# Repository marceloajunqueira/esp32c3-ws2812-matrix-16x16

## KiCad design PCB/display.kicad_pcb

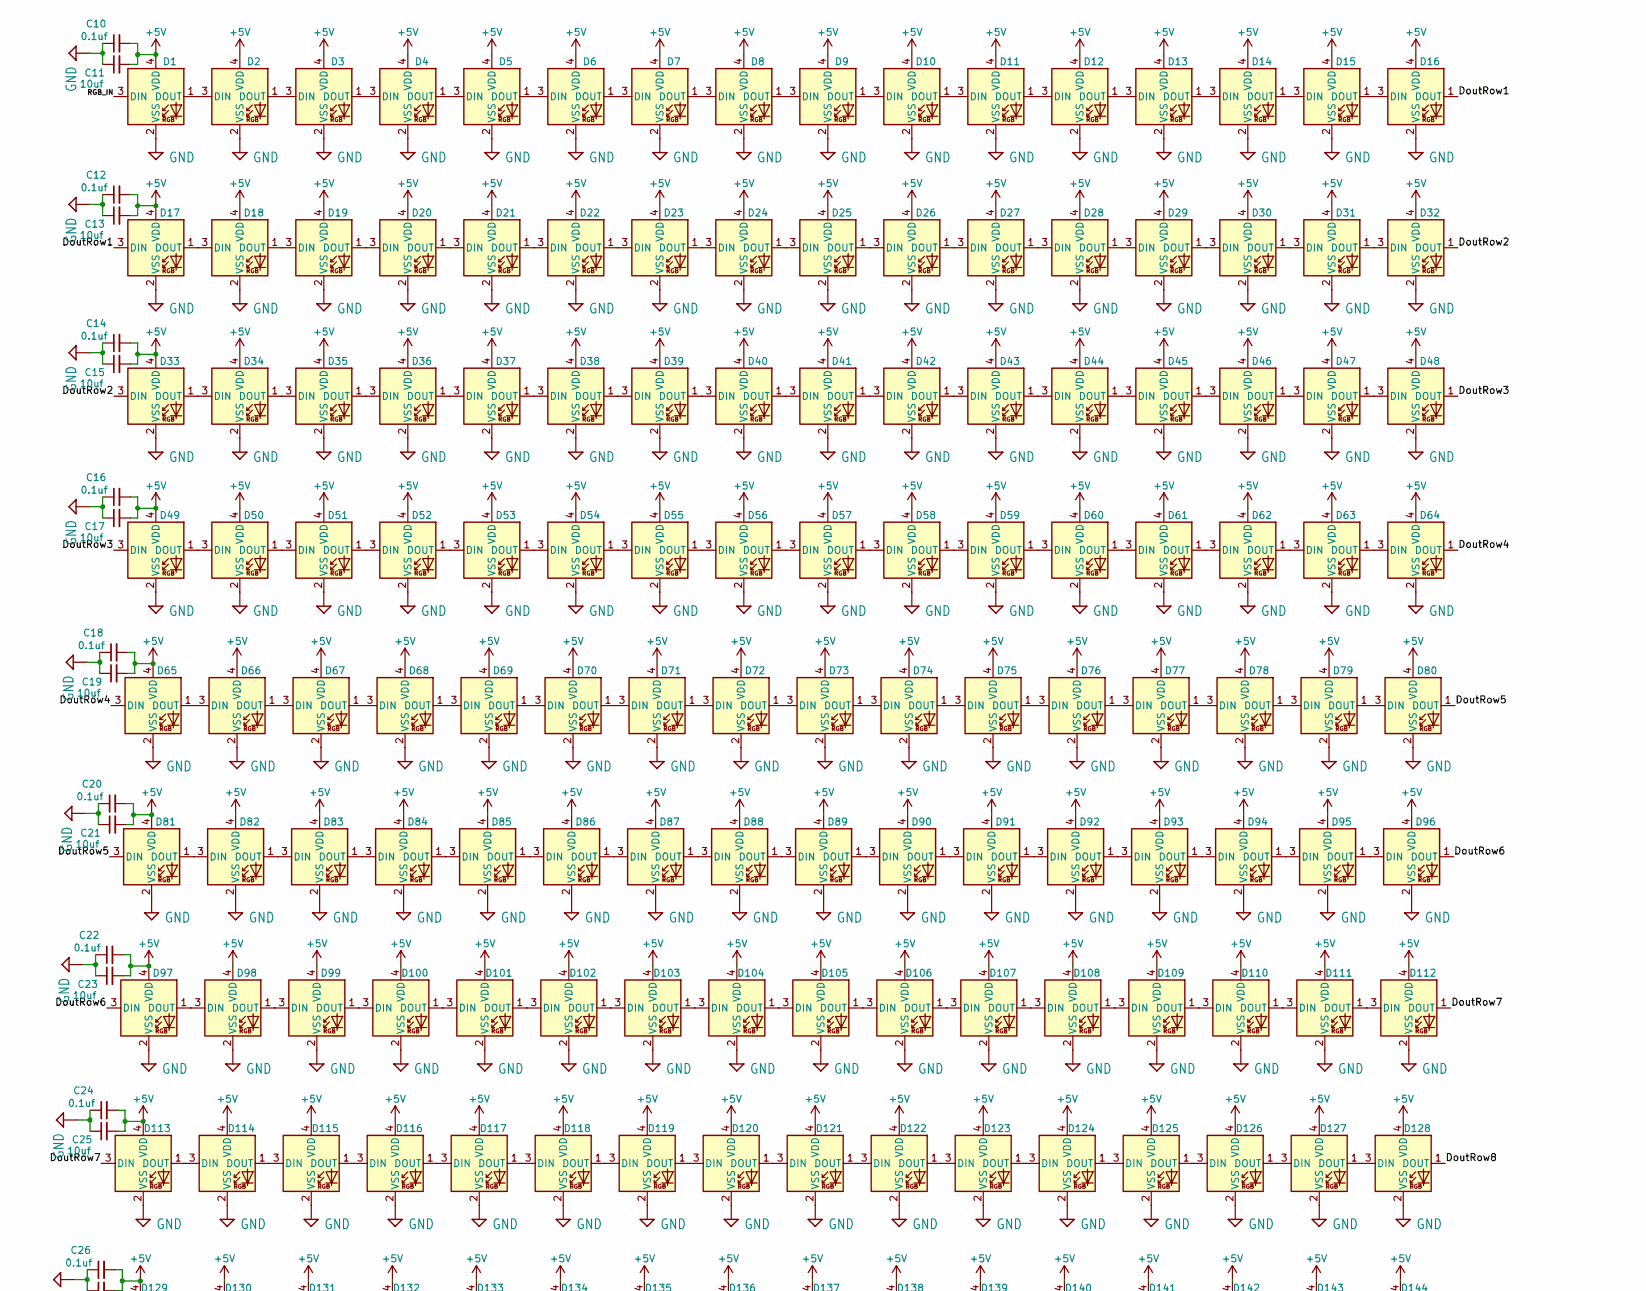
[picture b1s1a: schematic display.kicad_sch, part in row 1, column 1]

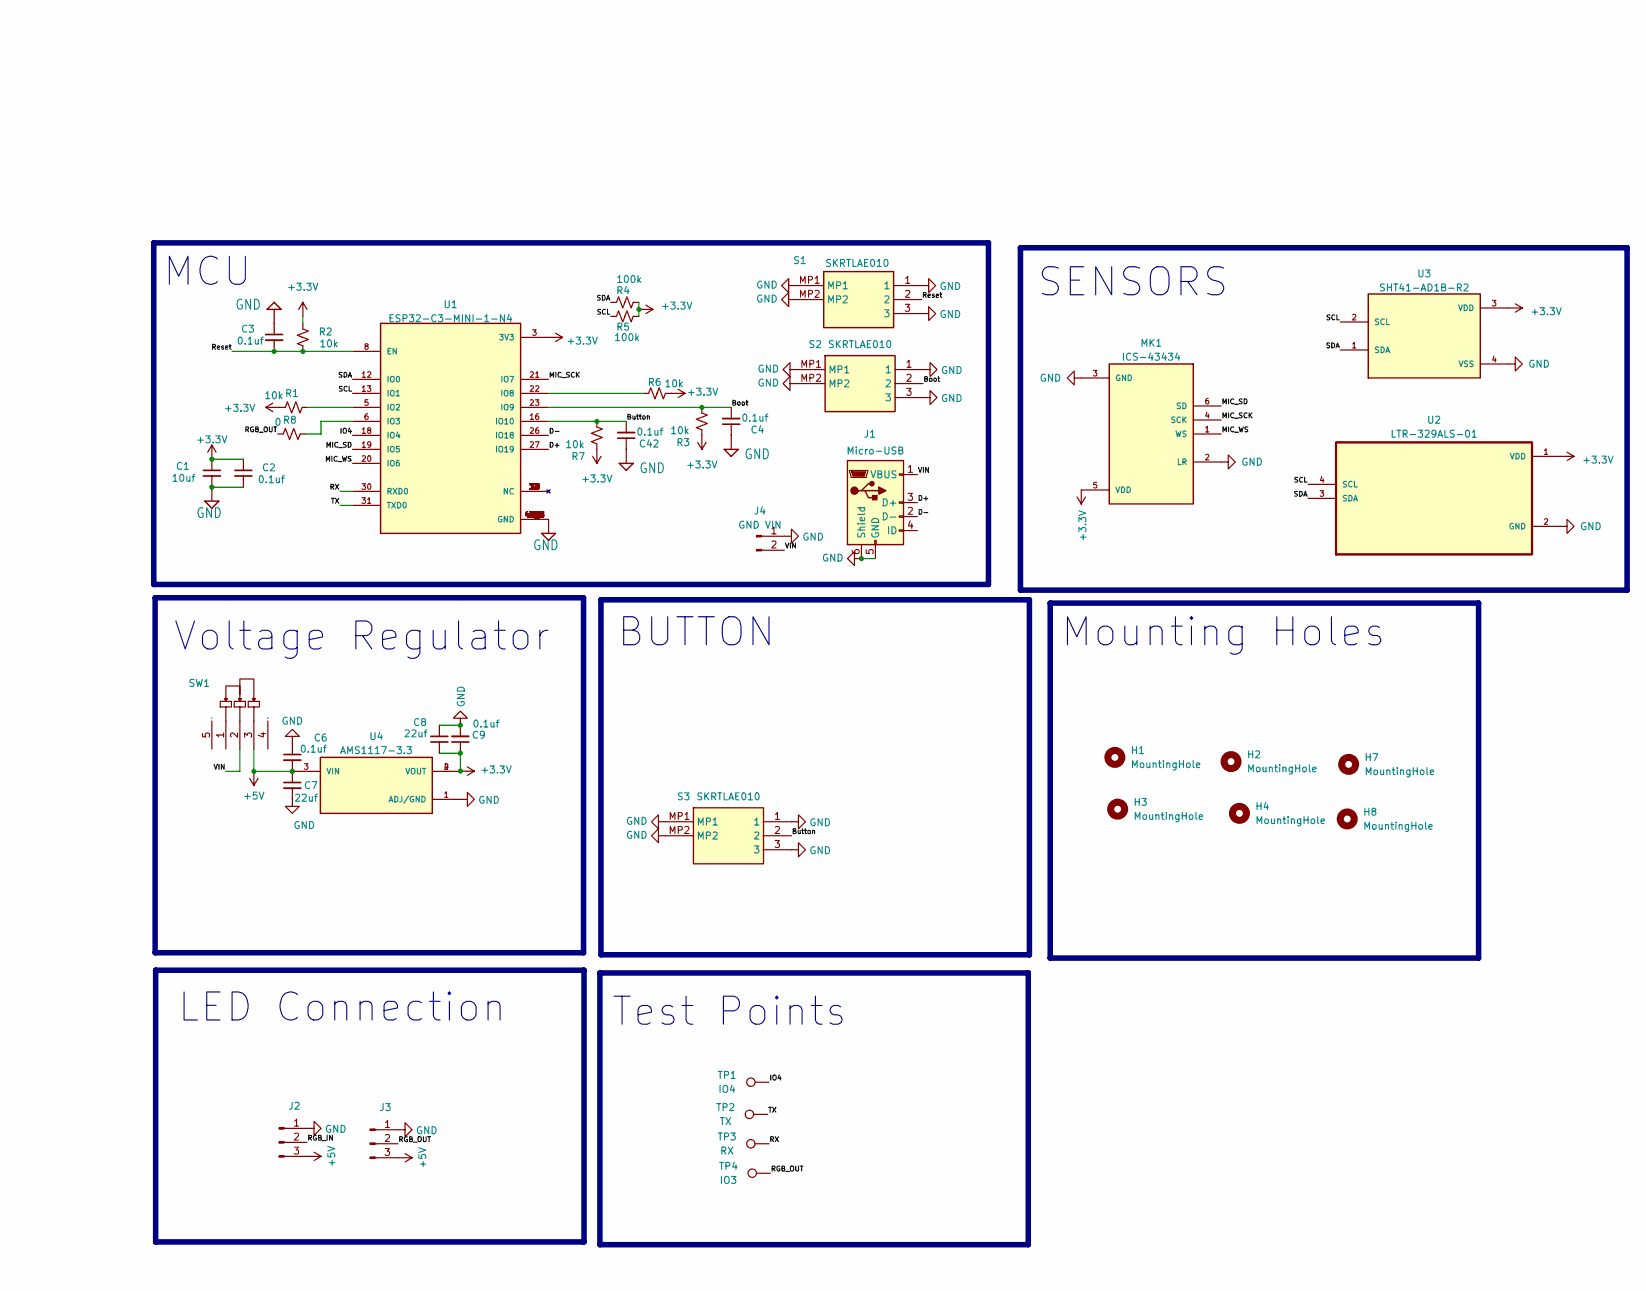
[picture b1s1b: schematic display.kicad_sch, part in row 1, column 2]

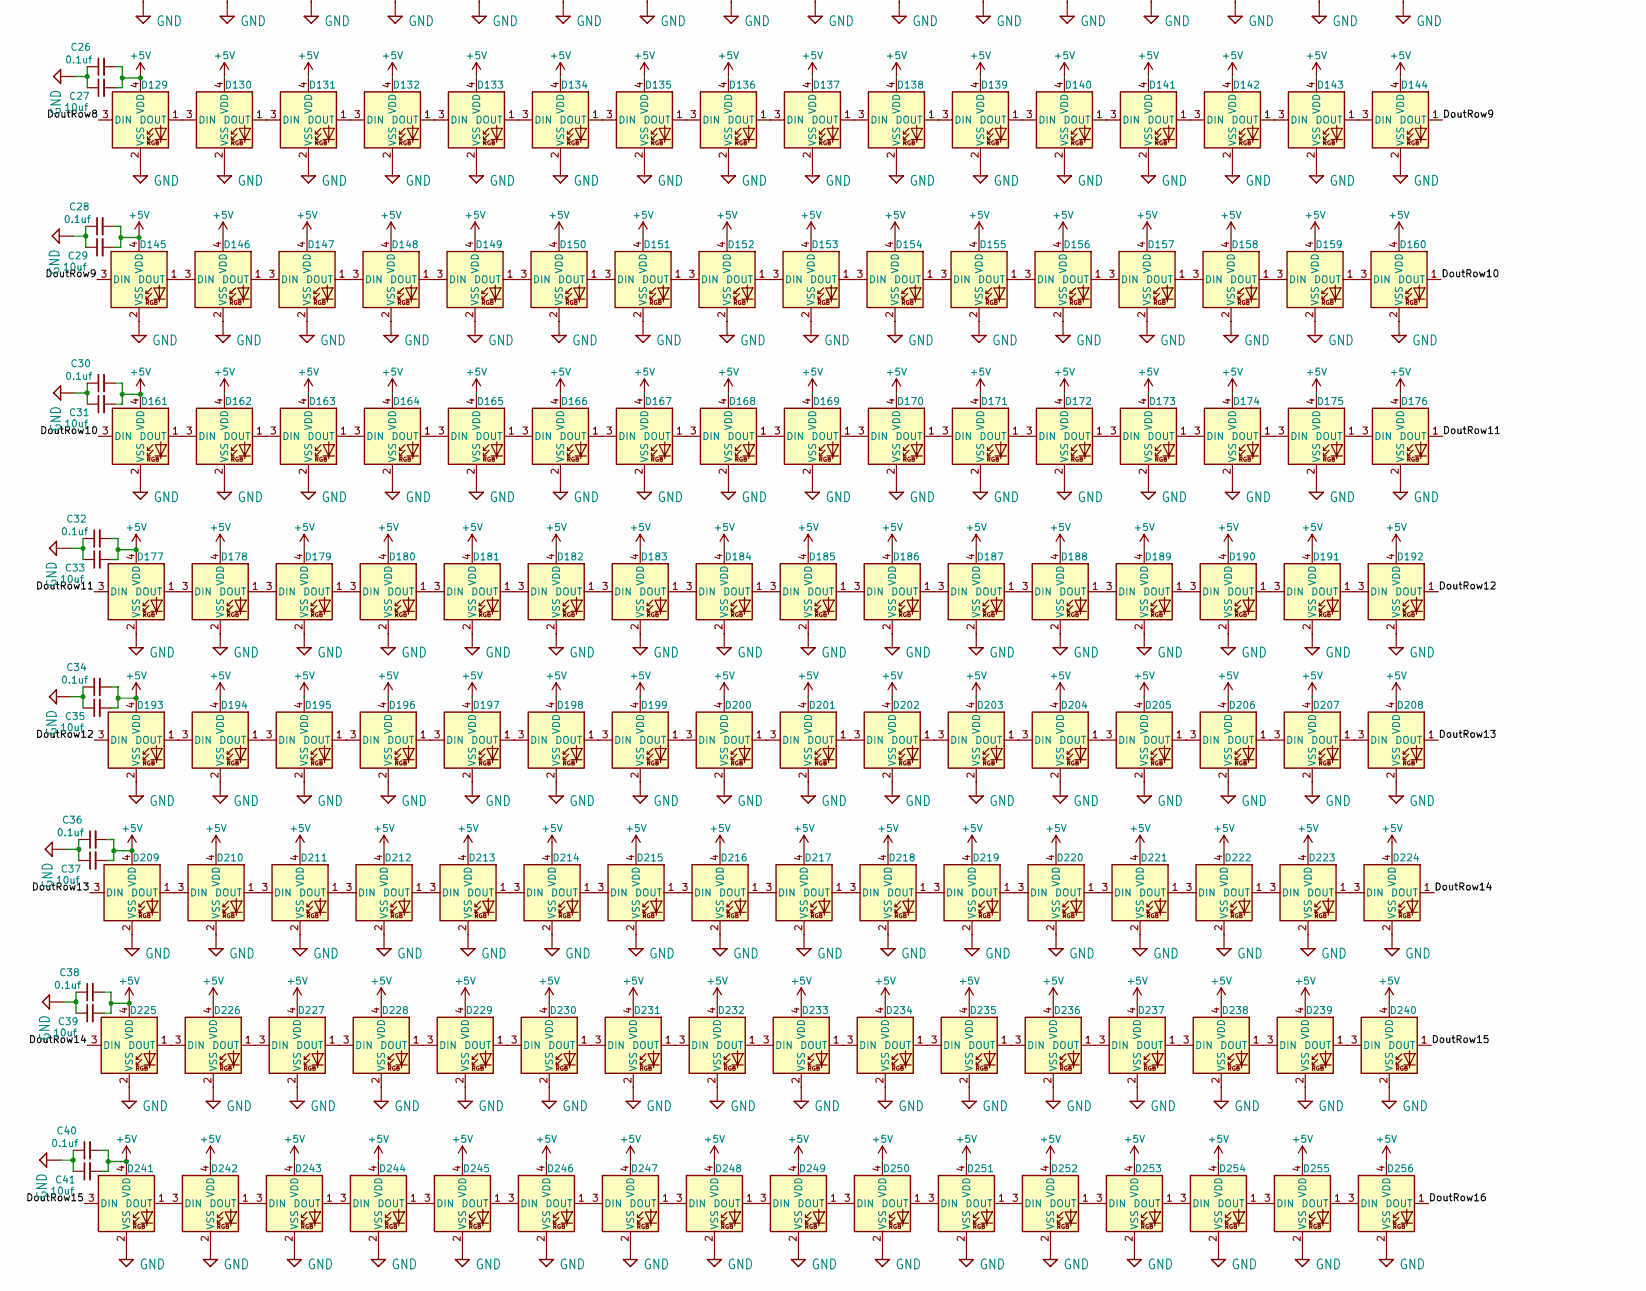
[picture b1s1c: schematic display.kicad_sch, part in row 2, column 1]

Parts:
C1: 10uf; C_0603_1608Metric; MPN CC0603MRX5R6BB106
C2, C3, C4, C6, C9, C10, C12, C14, C16, C18, C20, C22, C24, C26, C28, C30, C32, C34, C36, C38, C40, C42: 0.1uf; C_0603_1608Metric; MPN CC0603KRX7R9BB104
C7, C8: 22uf; C_1206_3216Metric; MPN T55A226M6R3C0500
C11, C13, C15, C17, C19, C21, C23, C25, C27, C29, C31, C33, C35, C37, C39, C41: 10uf; C_0603_1608Metric; MPN CC0603KRX7R9BB104
D1, D2, D3, D4, D5, D6, D7, D8, D9, D10, D11, D12, D13, D14, D15, D16, D17, D18, D19, D20, D21, D22, D23, D24, D25, D26, D27, D28, D29, D30, D31, D32, D33, D34, D35, D36, D37, D38, D39, D40, D41, D42, D43, D44, D45, D46, D47, D48, D49, D50, D51, D52, D53, D54, D55, D56, D57, D58, D59, D60, D61, D62, D63, D64, D65, D66, D67, D68, D69, D70, D71, D72, D73, D74, D75, D76, D77, D78, D79, D80, D81, D82, D83, D84, D85, D86, D87, D88, D89, D90, D91, D92, D93, D94, D95, D96, D97, D98, D99, D100, D101, D102, D103, D104, D105, D106, D107, D108, D109, D110, D111, D112, D113, D114, D115, D116, D117, D118, D119, D120, D121, D122, D123, D124, D125, D126, D127, D128, D129, D130, D131, D132, D133, D134, D135, D136, D137, D138, D139, D140, D141, D142, D143, D144, D145, D146, D147, D148, D149, D150, D151, D152, D153, D154, D155, D156, D157, D158, D159, D160, D161, D162, D163, D164, D165, D166, D167, D168, D169, D170, D171, D172, D173, D174, D175, D176, D177, D178, D179, D180, D181, D182, D183, D184, D185, D186, D187, D188, D189, D190, D191, D192, D193, D194, D195, D196, D197, D198, D199, D200, D201, D202, D203, D204, D205, D206, D207, D208, D209, D210, D211, D212, D213, D214, D215, D216, D217, D218, D219, D220, D221, D222, D223, D224, D225, D226, D227, D228, D229, D230, D231, D232, D233, D234, D235, D236, D237, D238, D239, D240, D241, D242, D243, D244, D245, D246, D247, D248, D249, D250, D251, D252, D253, D254, D255, D256: WS2812B-2020; WS2812B2020
H1, H2, H3, H4, H7, H8: MountingHole; MountingHole_2.7mm_M2.5_DIN965
J1: Micro-USB; USB_Micro-B_Molex-105017-0001; MPN 105017-0001
J2, J3: Conn_01x03_Pin; PinHeader_1x03_P2.54mm_Vertical
J4: GND VIN; PinHeader_1x02_P2.54mm_Vertical
MK1: ICS-43434; MIC_ICS-43434; MPN ICS-43434
R1, R2, R3, R6, R7: 10k; R_0603_1608Metric; MPN RC0603FR-0710KL
R4, R5: 100k; R_0603_1608Metric; MPN RC0603FR-07100KL
R8: 0; R_0603_1608Metric; MPN RC0603FR-0710KL
S1, S2, S3: SKRTLAE010; MPN SKRTLAE010
SW1: SW-TH_SK12D07VG3; MPN SK12D07VG3
TP1: IO4; TestPoint_Pad_D1.0mm
TP2: TX; TestPoint_Pad_D1.0mm
TP3: RX; TestPoint_Pad_D1.0mm
TP4: IO3; TestPoint_Pad_D1.0mm
U1: ESP32-C3-MINI-1-N4; XCVR_ESP32-C3-MINI-1-N4; MPN ESP32-C3-MINI-1-N4
U2: LTR-329ALS-01; SENSOR_LTR-329ALS-01; MPN LTR-329ALS-01
U3: SHT41-AD1B-R2; SHT4X; MPN SHT41-AD1B-R2
U4: AMS1117-3.3; SOT229P700X180-4N; MPN AMS1117-3.3

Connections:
+3.3V: C1.1, C2.1, C8.2, C9.1, MK1.5 (VDD), R1.2, R2.2, R3.2, R4.1, R5.1, R6.2, R7.2, U1.3 (3V3), U2.1 (VDD), U3.3 (VDD), U4.2 (VOUT), U4.4 (VOUT)
+5V: C6.2, C7.1, C10.2, C11.2, C12.2, C13.2, C14.2, C15.2, C16.2, C17.2, C18.2, C19.2, C20.2, C21.2, C22.2, C23.2, C24.2, C25.2, C26.2, C27.2, C28.2, C29.2, C30.2, C31.2, C32.2, C33.2, C34.2, C35.2, C36.2, C37.2, C38.2, C39.2, C40.2, C41.2, D1.4 (VDD), D2.4 (VDD), D3.4 (VDD), D4.4 (VDD), D5.4 (VDD), D6.4 (VDD), D7.4 (VDD), D8.4 (VDD), D9.4 (VDD), D10.4 (VDD), D11.4 (VDD), D12.4 (VDD), D13.4 (VDD), D14.4 (VDD), D15.4 (VDD), D16.4 (VDD), D17.4 (VDD), D18.4 (VDD), D19.4 (VDD), D20.4 (VDD), D21.4 (VDD), D22.4 (VDD), D23.4 (VDD), D24.4 (VDD), D25.4 (VDD), D26.4 (VDD), D27.4 (VDD), D28.4 (VDD), D29.4 (VDD), D30.4 (VDD), D31.4 (VDD), D32.4 (VDD), D33.4 (VDD), D34.4 (VDD), D35.4 (VDD), D36.4 (VDD), D37.4 (VDD), D38.4 (VDD), D39.4 (VDD), D40.4 (VDD), D41.4 (VDD), D42.4 (VDD), D43.4 (VDD), D44.4 (VDD), D45.4 (VDD), D46.4 (VDD), D47.4 (VDD), D48.4 (VDD), D49.4 (VDD), D50.4 (VDD), D51.4 (VDD), D52.4 (VDD), D53.4 (VDD), D54.4 (VDD), D55.4 (VDD), D56.4 (VDD), D57.4 (VDD), D58.4 (VDD), D59.4 (VDD), D60.4 (VDD), D61.4 (VDD), D62.4 (VDD), D63.4 (VDD), D64.4 (VDD), D65.4 (VDD), D66.4 (VDD), D67.4 (VDD), D68.4 (VDD), D69.4 (VDD), D70.4 (VDD), D71.4 (VDD), D72.4 (VDD), D73.4 (VDD), D74.4 (VDD), D75.4 (VDD), D76.4 (VDD), D77.4 (VDD), D78.4 (VDD), D79.4 (VDD), D80.4 (VDD), D81.4 (VDD), D82.4 (VDD), D83.4 (VDD), D84.4 (VDD), D85.4 (VDD), D86.4 (VDD), D87.4 (VDD), D88.4 (VDD), D89.4 (VDD), D90.4 (VDD), D91.4 (VDD), D92.4 (VDD), D93.4 (VDD), D94.4 (VDD), D95.4 (VDD), D96.4 (VDD), D97.4 (VDD), D98.4 (VDD), D99.4 (VDD), D100.4 (VDD), D101.4 (VDD), D102.4 (VDD), D103.4 (VDD), D104.4 (VDD), D105.4 (VDD), D106.4 (VDD), D107.4 (VDD), D108.4 (VDD), D109.4 (VDD), D110.4 (VDD), D111.4 (VDD), D112.4 (VDD), D113.4 (VDD), D114.4 (VDD), D115.4 (VDD), D116.4 (VDD), D117.4 (VDD), D118.4 (VDD), D119.4 (VDD), D120.4 (VDD), D121.4 (VDD), D122.4 (VDD), D123.4 (VDD), D124.4 (VDD), D125.4 (VDD), D126.4 (VDD), D127.4 (VDD), D128.4 (VDD), D129.4 (VDD), D130.4 (VDD), D131.4 (VDD), D132.4 (VDD), D133.4 (VDD), D134.4 (VDD), D135.4 (VDD), D136.4 (VDD), D137.4 (VDD), D138.4 (VDD), D139.4 (VDD), D140.4 (VDD), D141.4 (VDD), D142.4 (VDD), D143.4 (VDD), D144.4 (VDD), D145.4 (VDD), D146.4 (VDD), D147.4 (VDD), D148.4 (VDD), D149.4 (VDD), D150.4 (VDD), D151.4 (VDD), D152.4 (VDD), D153.4 (VDD), D154.4 (VDD), D155.4 (VDD), D156.4 (VDD), D157.4 (VDD), D158.4 (VDD), D159.4 (VDD), D160.4 (VDD), D161.4 (VDD), D162.4 (VDD), D163.4 (VDD), D164.4 (VDD), D165.4 (VDD), D166.4 (VDD), D167.4 (VDD), D168.4 (VDD), D169.4 (VDD), D170.4 (VDD), D171.4 (VDD), D172.4 (VDD), D173.4 (VDD), D174.4 (VDD), D175.4 (VDD), D176.4 (VDD), D177.4 (VDD), D178.4 (VDD), D179.4 (VDD), D180.4 (VDD), D181.4 (VDD), D182.4 (VDD), D183.4 (VDD), D184.4 (VDD), D185.4 (VDD), D186.4 (VDD), D187.4 (VDD), D188.4 (VDD), D189.4 (VDD), D190.4 (VDD), D191.4 (VDD), D192.4 (VDD), D193.4 (VDD), D194.4 (VDD), D195.4 (VDD), D196.4 (VDD), D197.4 (VDD), D198.4 (VDD), D199.4 (VDD), D200.4 (VDD), D201.4 (VDD), D202.4 (VDD), D203.4 (VDD), D204.4 (VDD), D205.4 (VDD), D206.4 (VDD), D207.4 (VDD), D208.4 (VDD), D209.4 (VDD), D210.4 (VDD), D211.4 (VDD), D212.4 (VDD), D213.4 (VDD), D214.4 (VDD), D215.4 (VDD), D216.4 (VDD), D217.4 (VDD), D218.4 (VDD), D219.4 (VDD), D220.4 (VDD), D221.4 (VDD), D222.4 (VDD), D223.4 (VDD), D224.4 (VDD), D225.4 (VDD), D226.4 (VDD), D227.4 (VDD), D228.4 (VDD), D229.4 (VDD), D230.4 (VDD), D231.4 (VDD), D232.4 (VDD), D233.4 (VDD), D234.4 (VDD), D235.4 (VDD), D236.4 (VDD), D237.4 (VDD), D238.4 (VDD), D239.4 (VDD), D240.4 (VDD), D241.4 (VDD), D242.4 (VDD), D243.4 (VDD), D244.4 (VDD), D245.4 (VDD), D246.4 (VDD), D247.4 (VDD), D248.4 (VDD), D249.4 (VDD), D250.4 (VDD), D251.4 (VDD), D252.4 (VDD), D253.4 (VDD), D254.4 (VDD), D255.4 (VDD), D256.4 (VDD), J2.3, J3.3, SW1.3, U4.3 (VIN)
/Boot: C4.2, R3.1, S2.2, U1.23 (IO9)
/Button: C42.2, R7.1, S3.2, U1.16 (IO10)
/D+: J1.3 (D+), U1.27 (IO19)
/D-: J1.2 (D-), U1.26 (IO18)
/DoutRow1: D16.1 (DOUT), D17.3 (DIN)
/DoutRow2: D32.1 (DOUT), D33.3 (DIN)
/DoutRow3: D48.1 (DOUT), D49.3 (DIN)
/DoutRow4: D64.1 (DOUT), D65.3 (DIN)
/DoutRow5: D80.1 (DOUT), D81.3 (DIN)
/DoutRow6: D96.1 (DOUT), D97.3 (DIN)
/DoutRow7: D112.1 (DOUT), D113.3 (DIN)
/DoutRow8: D128.1 (DOUT), D129.3 (DIN)
/DoutRow9: D144.1 (DOUT), D145.3 (DIN)
/DoutRow10: D160.1 (DOUT), D161.3 (DIN)
/DoutRow11: D176.1 (DOUT), D177.3 (DIN)
/DoutRow12: D192.1 (DOUT), D193.3 (DIN)
/DoutRow13: D208.1 (DOUT), D209.3 (DIN)
/DoutRow14: D224.1 (DOUT), D225.3 (DIN)
/DoutRow15: D240.1 (DOUT), D241.3 (DIN)
/DoutRow16: D256.1 (DOUT)
/IO4: TP1.1, U1.18 (IO4)
/MIC_SCK: MK1.4 (SCK), U1.21 (IO7)
/MIC_SD: MK1.6 (SD), U1.19 (IO5)
/MIC_WS: MK1.1 (WS), U1.20 (IO6)
/RGB_IN: D1.3 (DIN), J2.2
/RGB_OUT: J3.2, R8.2, TP4.1
/RX: TP3.1, U1.30 (RXD0)
/Reset: C3.2, R2.1, S1.2, U1.8 (EN)
/SCL: R5.2, U1.13 (IO1), U2.4 (SCL), U3.2 (SCL)
/SDA: R4.2, U1.12 (IO0), U2.3 (SDA), U3.1 (SDA)
/TX: TP2.1, U1.31 (TXD0)
/VIN: J1.1 (VBUS), J4.2, SW1.2
GND: C1.2, C2.2, C3.1, C4.1, C6.1, C7.2, C8.1, C9.2, C10.1, C11.1, C12.1, C13.1, C14.1, C15.1, C16.1, C17.1, C18.1, C19.1, C20.1, C21.1, C22.1, C23.1, C24.1, C25.1, C26.1, C27.1, C28.1, C29.1, C30.1, C31.1, C32.1, C33.1, C34.1, C35.1, C36.1, C37.1, C38.1, C39.1, C40.1, C41.1, C42.1, D1.2 (VSS), D2.2 (VSS), D3.2 (VSS), D4.2 (VSS), D5.2 (VSS), D6.2 (VSS), D7.2 (VSS), D8.2 (VSS), D9.2 (VSS), D10.2 (VSS), D11.2 (VSS), D12.2 (VSS), D13.2 (VSS), D14.2 (VSS), D15.2 (VSS), D16.2 (VSS), D17.2 (VSS), D18.2 (VSS), D19.2 (VSS), D20.2 (VSS), D21.2 (VSS), D22.2 (VSS), D23.2 (VSS), D24.2 (VSS), D25.2 (VSS), D26.2 (VSS), D27.2 (VSS), D28.2 (VSS), D29.2 (VSS), D30.2 (VSS), D31.2 (VSS), D32.2 (VSS), D33.2 (VSS), D34.2 (VSS), D35.2 (VSS), D36.2 (VSS), D37.2 (VSS), D38.2 (VSS), D39.2 (VSS), D40.2 (VSS), D41.2 (VSS), D42.2 (VSS), D43.2 (VSS), D44.2 (VSS), D45.2 (VSS), D46.2 (VSS), D47.2 (VSS), D48.2 (VSS), D49.2 (VSS), D50.2 (VSS), D51.2 (VSS), D52.2 (VSS), D53.2 (VSS), D54.2 (VSS), D55.2 (VSS), D56.2 (VSS), D57.2 (VSS), D58.2 (VSS), D59.2 (VSS), D60.2 (VSS), D61.2 (VSS), D62.2 (VSS), D63.2 (VSS), D64.2 (VSS), D65.2 (VSS), D66.2 (VSS), D67.2 (VSS), D68.2 (VSS), D69.2 (VSS), D70.2 (VSS), D71.2 (VSS), D72.2 (VSS), D73.2 (VSS), D74.2 (VSS), D75.2 (VSS), D76.2 (VSS), D77.2 (VSS), D78.2 (VSS), D79.2 (VSS), D80.2 (VSS), D81.2 (VSS), D82.2 (VSS), D83.2 (VSS), D84.2 (VSS), D85.2 (VSS), D86.2 (VSS), D87.2 (VSS), D88.2 (VSS), D89.2 (VSS), D90.2 (VSS), D91.2 (VSS), D92.2 (VSS), D93.2 (VSS), D94.2 (VSS), D95.2 (VSS), D96.2 (VSS), D97.2 (VSS), D98.2 (VSS), D99.2 (VSS), D100.2 (VSS), D101.2 (VSS), D102.2 (VSS), D103.2 (VSS), D104.2 (VSS), D105.2 (VSS), D106.2 (VSS), D107.2 (VSS), D108.2 (VSS), D109.2 (VSS), D110.2 (VSS), D111.2 (VSS), D112.2 (VSS), D113.2 (VSS), D114.2 (VSS), D115.2 (VSS), D116.2 (VSS), D117.2 (VSS), D118.2 (VSS), D119.2 (VSS), D120.2 (VSS), D121.2 (VSS), D122.2 (VSS), D123.2 (VSS), D124.2 (VSS), D125.2 (VSS), D126.2 (VSS), D127.2 (VSS), D128.2 (VSS), D129.2 (VSS), D130.2 (VSS), D131.2 (VSS), D132.2 (VSS), D133.2 (VSS), D134.2 (VSS), D135.2 (VSS), D136.2 (VSS), D137.2 (VSS), D138.2 (VSS), D139.2 (VSS), D140.2 (VSS), D141.2 (VSS), D142.2 (VSS), D143.2 (VSS), D144.2 (VSS), D145.2 (VSS), D146.2 (VSS), D147.2 (VSS), D148.2 (VSS), D149.2 (VSS), D150.2 (VSS), D151.2 (VSS), D152.2 (VSS), D153.2 (VSS), D154.2 (VSS), D155.2 (VSS), D156.2 (VSS), D157.2 (VSS), D158.2 (VSS), D159.2 (VSS), D160.2 (VSS), D161.2 (VSS), D162.2 (VSS), D163.2 (VSS), D164.2 (VSS), D165.2 (VSS), D166.2 (VSS), D167.2 (VSS), D168.2 (VSS), D169.2 (VSS), D170.2 (VSS), D171.2 (VSS), D172.2 (VSS), D173.2 (VSS), D174.2 (VSS), D175.2 (VSS), D176.2 (VSS), D177.2 (VSS), D178.2 (VSS), D179.2 (VSS), D180.2 (VSS), D181.2 (VSS), D182.2 (VSS), D183.2 (VSS), D184.2 (VSS), D185.2 (VSS), D186.2 (VSS), D187.2 (VSS), D188.2 (VSS), D189.2 (VSS), D190.2 (VSS), D191.2 (VSS), D192.2 (VSS), D193.2 (VSS), D194.2 (VSS), D195.2 (VSS), D196.2 (VSS), D197.2 (VSS), D198.2 (VSS), D199.2 (VSS), D200.2 (VSS), D201.2 (VSS), D202.2 (VSS), D203.2 (VSS), D204.2 (VSS), D205.2 (VSS), D206.2 (VSS), D207.2 (VSS), D208.2 (VSS), D209.2 (VSS), D210.2 (VSS), D211.2 (VSS), D212.2 (VSS), D213.2 (VSS), D214.2 (VSS), D215.2 (VSS), D216.2 (VSS), D217.2 (VSS), D218.2 (VSS), D219.2 (VSS), D220.2 (VSS), D221.2 (VSS), D222.2 (VSS), D223.2 (VSS), D224.2 (VSS), D225.2 (VSS), D226.2 (VSS), D227.2 (VSS), D228.2 (VSS), D229.2 (VSS), D230.2 (VSS), D231.2 (VSS), D232.2 (VSS), D233.2 (VSS), D234.2 (VSS), D235.2 (VSS), D236.2 (VSS), D237.2 (VSS), D238.2 (VSS), D239.2 (VSS), D240.2 (VSS), D241.2 (VSS), D242.2 (VSS), D243.2 (VSS), D244.2 (VSS), D245.2 (VSS), D246.2 (VSS), D247.2 (VSS), D248.2 (VSS), D249.2 (VSS), D250.2 (VSS), D251.2 (VSS), D252.2 (VSS), D253.2 (VSS), D254.2 (VSS), D255.2 (VSS), D256.2 (VSS), J1.5 (GND), J1.6 (Shield), J2.1, J3.1, J4.1, MK1.2 (LR), MK1.3 (GND), S1.1, S1.3, S1.MP1, S1.MP2, S2.1, S2.3, S2.MP1, S2.MP2, S3.1, S3.3, S3.MP1, S3.MP2, U1.1 (GND), U1.2 (GND), U1.11 (GND), U1.14 (GND), U1.36 (GND), U1.37 (GND), U1.38 (GND), U1.39 (GND), U1.40 (GND), U1.41 (GND), U1.42 (GND), U1.43 (GND), U1.44 (GND), U1.45 (GND), U1.46 (GND), U1.47 (GND), U1.48 (GND), U1.49_1 (GND), U1.49_2 (GND), U1.49_3 (GND), U1.49_4 (GND), U1.49_5 (GND), U1.49_6 (GND), U1.49_7 (GND), U1.49_8 (GND), U1.49_9 (GND), U1.50 (GND), U1.51 (GND), U1.52 (GND), U1.53 (GND), U2.2 (GND), U3.4 (VSS), U4.1 (ADJ/GND)
unnamed: D1.1 (DOUT), D2.3 (DIN)
unnamed: D2.1 (DOUT), D3.3 (DIN)
unnamed: D3.1 (DOUT), D4.3 (DIN)
unnamed: D4.1 (DOUT), D5.3 (DIN)
unnamed: D5.1 (DOUT), D6.3 (DIN)
unnamed: D6.1 (DOUT), D7.3 (DIN)
unnamed: D7.1 (DOUT), D8.3 (DIN)
unnamed: D8.1 (DOUT), D9.3 (DIN)
unnamed: D9.1 (DOUT), D10.3 (DIN)
unnamed: D10.1 (DOUT), D11.3 (DIN)
unnamed: D11.1 (DOUT), D12.3 (DIN)
unnamed: D12.1 (DOUT), D13.3 (DIN)
unnamed: D13.1 (DOUT), D14.3 (DIN)
unnamed: D14.1 (DOUT), D15.3 (DIN)
unnamed: D15.1 (DOUT), D16.3 (DIN)
unnamed: D17.1 (DOUT), D18.3 (DIN)
unnamed: D18.1 (DOUT), D19.3 (DIN)
unnamed: D19.1 (DOUT), D20.3 (DIN)
unnamed: D20.1 (DOUT), D21.3 (DIN)
unnamed: D21.1 (DOUT), D22.3 (DIN)
unnamed: D22.1 (DOUT), D23.3 (DIN)
unnamed: D23.1 (DOUT), D24.3 (DIN)
unnamed: D24.1 (DOUT), D25.3 (DIN)
unnamed: D25.1 (DOUT), D26.3 (DIN)
unnamed: D26.1 (DOUT), D27.3 (DIN)
unnamed: D27.1 (DOUT), D28.3 (DIN)
unnamed: D28.1 (DOUT), D29.3 (DIN)
unnamed: D29.1 (DOUT), D30.3 (DIN)
unnamed: D30.1 (DOUT), D31.3 (DIN)
unnamed: D31.1 (DOUT), D32.3 (DIN)
unnamed: D33.1 (DOUT), D34.3 (DIN)
unnamed: D34.1 (DOUT), D35.3 (DIN)
unnamed: D35.1 (DOUT), D36.3 (DIN)
unnamed: D36.1 (DOUT), D37.3 (DIN)
unnamed: D37.1 (DOUT), D38.3 (DIN)
unnamed: D38.1 (DOUT), D39.3 (DIN)
unnamed: D39.1 (DOUT), D40.3 (DIN)
unnamed: D40.1 (DOUT), D41.3 (DIN)
unnamed: D41.1 (DOUT), D42.3 (DIN)
unnamed: D42.1 (DOUT), D43.3 (DIN)
unnamed: D43.1 (DOUT), D44.3 (DIN)
unnamed: D44.1 (DOUT), D45.3 (DIN)
unnamed: D45.1 (DOUT), D46.3 (DIN)
unnamed: D46.1 (DOUT), D47.3 (DIN)
unnamed: D47.1 (DOUT), D48.3 (DIN)
unnamed: D49.1 (DOUT), D50.3 (DIN)
unnamed: D50.1 (DOUT), D51.3 (DIN)
unnamed: D51.1 (DOUT), D52.3 (DIN)
unnamed: D52.1 (DOUT), D53.3 (DIN)
unnamed: D53.1 (DOUT), D54.3 (DIN)
unnamed: D54.1 (DOUT), D55.3 (DIN)
unnamed: D55.1 (DOUT), D56.3 (DIN)
unnamed: D56.1 (DOUT), D57.3 (DIN)
unnamed: D57.1 (DOUT), D58.3 (DIN)
unnamed: D58.1 (DOUT), D59.3 (DIN)
unnamed: D59.1 (DOUT), D60.3 (DIN)
unnamed: D60.1 (DOUT), D61.3 (DIN)
unnamed: D61.1 (DOUT), D62.3 (DIN)
unnamed: D62.1 (DOUT), D63.3 (DIN)
unnamed: D63.1 (DOUT), D64.3 (DIN)
unnamed: D65.1 (DOUT), D66.3 (DIN)
unnamed: D66.1 (DOUT), D67.3 (DIN)
unnamed: D67.1 (DOUT), D68.3 (DIN)
unnamed: D68.1 (DOUT), D69.3 (DIN)
unnamed: D69.1 (DOUT), D70.3 (DIN)
unnamed: D70.1 (DOUT), D71.3 (DIN)
unnamed: D71.1 (DOUT), D72.3 (DIN)
unnamed: D72.1 (DOUT), D73.3 (DIN)
unnamed: D73.1 (DOUT), D74.3 (DIN)
unnamed: D74.1 (DOUT), D75.3 (DIN)
unnamed: D75.1 (DOUT), D76.3 (DIN)
unnamed: D76.1 (DOUT), D77.3 (DIN)
unnamed: D77.1 (DOUT), D78.3 (DIN)
unnamed: D78.1 (DOUT), D79.3 (DIN)
unnamed: D79.1 (DOUT), D80.3 (DIN)
unnamed: D81.1 (DOUT), D82.3 (DIN)
unnamed: D82.1 (DOUT), D83.3 (DIN)
unnamed: D83.1 (DOUT), D84.3 (DIN)
unnamed: D84.1 (DOUT), D85.3 (DIN)
unnamed: D85.1 (DOUT), D86.3 (DIN)
unnamed: D86.1 (DOUT), D87.3 (DIN)
unnamed: D87.1 (DOUT), D88.3 (DIN)
unnamed: D88.1 (DOUT), D89.3 (DIN)
unnamed: D89.1 (DOUT), D90.3 (DIN)
unnamed: D90.1 (DOUT), D91.3 (DIN)
unnamed: D91.1 (DOUT), D92.3 (DIN)
unnamed: D92.1 (DOUT), D93.3 (DIN)
unnamed: D93.1 (DOUT), D94.3 (DIN)
unnamed: D94.1 (DOUT), D95.3 (DIN)
unnamed: D95.1 (DOUT), D96.3 (DIN)
unnamed: D97.1 (DOUT), D98.3 (DIN)
unnamed: D98.1 (DOUT), D99.3 (DIN)
unnamed: D99.1 (DOUT), D100.3 (DIN)
unnamed: D100.1 (DOUT), D101.3 (DIN)
unnamed: D101.1 (DOUT), D102.3 (DIN)
unnamed: D102.1 (DOUT), D103.3 (DIN)
unnamed: D103.1 (DOUT), D104.3 (DIN)
unnamed: D104.1 (DOUT), D105.3 (DIN)
unnamed: D105.1 (DOUT), D106.3 (DIN)
unnamed: D106.1 (DOUT), D107.3 (DIN)
unnamed: D107.1 (DOUT), D108.3 (DIN)
unnamed: D108.1 (DOUT), D109.3 (DIN)
unnamed: D109.1 (DOUT), D110.3 (DIN)
unnamed: D110.1 (DOUT), D111.3 (DIN)
unnamed: D111.1 (DOUT), D112.3 (DIN)
unnamed: D113.1 (DOUT), D114.3 (DIN)
unnamed: D114.1 (DOUT), D115.3 (DIN)
unnamed: D115.1 (DOUT), D116.3 (DIN)
unnamed: D116.1 (DOUT), D117.3 (DIN)
unnamed: D117.1 (DOUT), D118.3 (DIN)
unnamed: D118.1 (DOUT), D119.3 (DIN)
unnamed: D119.1 (DOUT), D120.3 (DIN)
unnamed: D120.1 (DOUT), D121.3 (DIN)
unnamed: D121.1 (DOUT), D122.3 (DIN)
unnamed: D122.1 (DOUT), D123.3 (DIN)
unnamed: D123.1 (DOUT), D124.3 (DIN)
unnamed: D124.1 (DOUT), D125.3 (DIN)
unnamed: D125.1 (DOUT), D126.3 (DIN)
unnamed: D126.1 (DOUT), D127.3 (DIN)
unnamed: D127.1 (DOUT), D128.3 (DIN)
unnamed: D129.1 (DOUT), D130.3 (DIN)
unnamed: D130.1 (DOUT), D131.3 (DIN)
unnamed: D131.1 (DOUT), D132.3 (DIN)
unnamed: D132.1 (DOUT), D133.3 (DIN)
unnamed: D133.1 (DOUT), D134.3 (DIN)
unnamed: D134.1 (DOUT), D135.3 (DIN)
unnamed: D135.1 (DOUT), D136.3 (DIN)
unnamed: D136.1 (DOUT), D137.3 (DIN)
unnamed: D137.1 (DOUT), D138.3 (DIN)
unnamed: D138.1 (DOUT), D139.3 (DIN)
unnamed: D139.1 (DOUT), D140.3 (DIN)
unnamed: D140.1 (DOUT), D141.3 (DIN)
unnamed: D141.1 (DOUT), D142.3 (DIN)
unnamed: D142.1 (DOUT), D143.3 (DIN)
unnamed: D143.1 (DOUT), D144.3 (DIN)
unnamed: D145.1 (DOUT), D146.3 (DIN)
unnamed: D146.1 (DOUT), D147.3 (DIN)
unnamed: D147.1 (DOUT), D148.3 (DIN)
unnamed: D148.1 (DOUT), D149.3 (DIN)
unnamed: D149.1 (DOUT), D150.3 (DIN)
unnamed: D150.1 (DOUT), D151.3 (DIN)
unnamed: D151.1 (DOUT), D152.3 (DIN)
unnamed: D152.1 (DOUT), D153.3 (DIN)
unnamed: D153.1 (DOUT), D154.3 (DIN)
unnamed: D154.1 (DOUT), D155.3 (DIN)
unnamed: D155.1 (DOUT), D156.3 (DIN)
unnamed: D156.1 (DOUT), D157.3 (DIN)
unnamed: D157.1 (DOUT), D158.3 (DIN)
unnamed: D158.1 (DOUT), D159.3 (DIN)
unnamed: D159.1 (DOUT), D160.3 (DIN)
unnamed: D161.1 (DOUT), D162.3 (DIN)
unnamed: D162.1 (DOUT), D163.3 (DIN)
unnamed: D163.1 (DOUT), D164.3 (DIN)
unnamed: D164.1 (DOUT), D165.3 (DIN)
unnamed: D165.1 (DOUT), D166.3 (DIN)
unnamed: D166.1 (DOUT), D167.3 (DIN)
unnamed: D167.1 (DOUT), D168.3 (DIN)
unnamed: D168.1 (DOUT), D169.3 (DIN)
unnamed: D169.1 (DOUT), D170.3 (DIN)
unnamed: D170.1 (DOUT), D171.3 (DIN)
unnamed: D171.1 (DOUT), D172.3 (DIN)
unnamed: D172.1 (DOUT), D173.3 (DIN)
unnamed: D173.1 (DOUT), D174.3 (DIN)
unnamed: D174.1 (DOUT), D175.3 (DIN)
unnamed: D175.1 (DOUT), D176.3 (DIN)
unnamed: D177.1 (DOUT), D178.3 (DIN)
unnamed: D178.1 (DOUT), D179.3 (DIN)
unnamed: D179.1 (DOUT), D180.3 (DIN)
unnamed: D180.1 (DOUT), D181.3 (DIN)
unnamed: D181.1 (DOUT), D182.3 (DIN)
unnamed: D182.1 (DOUT), D183.3 (DIN)
unnamed: D183.1 (DOUT), D184.3 (DIN)
unnamed: D184.1 (DOUT), D185.3 (DIN)
unnamed: D185.1 (DOUT), D186.3 (DIN)
unnamed: D186.1 (DOUT), D187.3 (DIN)
unnamed: D187.1 (DOUT), D188.3 (DIN)
unnamed: D188.1 (DOUT), D189.3 (DIN)
unnamed: D189.1 (DOUT), D190.3 (DIN)
unnamed: D190.1 (DOUT), D191.3 (DIN)
unnamed: D191.1 (DOUT), D192.3 (DIN)
unnamed: D193.1 (DOUT), D194.3 (DIN)
unnamed: D194.1 (DOUT), D195.3 (DIN)
unnamed: D195.1 (DOUT), D196.3 (DIN)
unnamed: D196.1 (DOUT), D197.3 (DIN)
unnamed: D197.1 (DOUT), D198.3 (DIN)
unnamed: D198.1 (DOUT), D199.3 (DIN)
unnamed: D199.1 (DOUT), D200.3 (DIN)
unnamed: D200.1 (DOUT), D201.3 (DIN)
unnamed: D201.1 (DOUT), D202.3 (DIN)
unnamed: D202.1 (DOUT), D203.3 (DIN)
unnamed: D203.1 (DOUT), D204.3 (DIN)
unnamed: D204.1 (DOUT), D205.3 (DIN)
unnamed: D205.1 (DOUT), D206.3 (DIN)
unnamed: D206.1 (DOUT), D207.3 (DIN)
unnamed: D207.1 (DOUT), D208.3 (DIN)
unnamed: D209.1 (DOUT), D210.3 (DIN)
unnamed: D210.1 (DOUT), D211.3 (DIN)
unnamed: D211.1 (DOUT), D212.3 (DIN)
unnamed: D212.1 (DOUT), D213.3 (DIN)
unnamed: D213.1 (DOUT), D214.3 (DIN)
unnamed: D214.1 (DOUT), D215.3 (DIN)
unnamed: D215.1 (DOUT), D216.3 (DIN)
unnamed: D216.1 (DOUT), D217.3 (DIN)
unnamed: D217.1 (DOUT), D218.3 (DIN)
unnamed: D218.1 (DOUT), D219.3 (DIN)
unnamed: D219.1 (DOUT), D220.3 (DIN)
unnamed: D220.1 (DOUT), D221.3 (DIN)
unnamed: D221.1 (DOUT), D222.3 (DIN)
unnamed: D222.1 (DOUT), D223.3 (DIN)
unnamed: D223.1 (DOUT), D224.3 (DIN)
unnamed: D225.1 (DOUT), D226.3 (DIN)
unnamed: D226.1 (DOUT), D227.3 (DIN)
unnamed: D227.1 (DOUT), D228.3 (DIN)
unnamed: D228.1 (DOUT), D229.3 (DIN)
unnamed: D229.1 (DOUT), D230.3 (DIN)
unnamed: D230.1 (DOUT), D231.3 (DIN)
unnamed: D231.1 (DOUT), D232.3 (DIN)
unnamed: D232.1 (DOUT), D233.3 (DIN)
unnamed: D233.1 (DOUT), D234.3 (DIN)
unnamed: D234.1 (DOUT), D235.3 (DIN)
unnamed: D235.1 (DOUT), D236.3 (DIN)
unnamed: D236.1 (DOUT), D237.3 (DIN)
unnamed: D237.1 (DOUT), D238.3 (DIN)
unnamed: D238.1 (DOUT), D239.3 (DIN)
unnamed: D239.1 (DOUT), D240.3 (DIN)
unnamed: D241.1 (DOUT), D242.3 (DIN)
unnamed: D242.1 (DOUT), D243.3 (DIN)
unnamed: D243.1 (DOUT), D244.3 (DIN)
unnamed: D244.1 (DOUT), D245.3 (DIN)
unnamed: D245.1 (DOUT), D246.3 (DIN)
unnamed: D246.1 (DOUT), D247.3 (DIN)
unnamed: D247.1 (DOUT), D248.3 (DIN)
unnamed: D248.1 (DOUT), D249.3 (DIN)
unnamed: D249.1 (DOUT), D250.3 (DIN)
unnamed: D250.1 (DOUT), D251.3 (DIN)
unnamed: D251.1 (DOUT), D252.3 (DIN)
unnamed: D252.1 (DOUT), D253.3 (DIN)
unnamed: D253.1 (DOUT), D254.3 (DIN)
unnamed: D254.1 (DOUT), D255.3 (DIN)
unnamed: D255.1 (DOUT), D256.3 (DIN)
unnamed: R1.1, U1.5 (IO2)
unnamed: R8.1, U1.6 (IO3)
unnamed: R6.1, U1.22 (IO8)

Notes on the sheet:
SENSORS
Voltage Regulator
Test Points
Mounting Holes
LED Connection
BUTTON
MCU

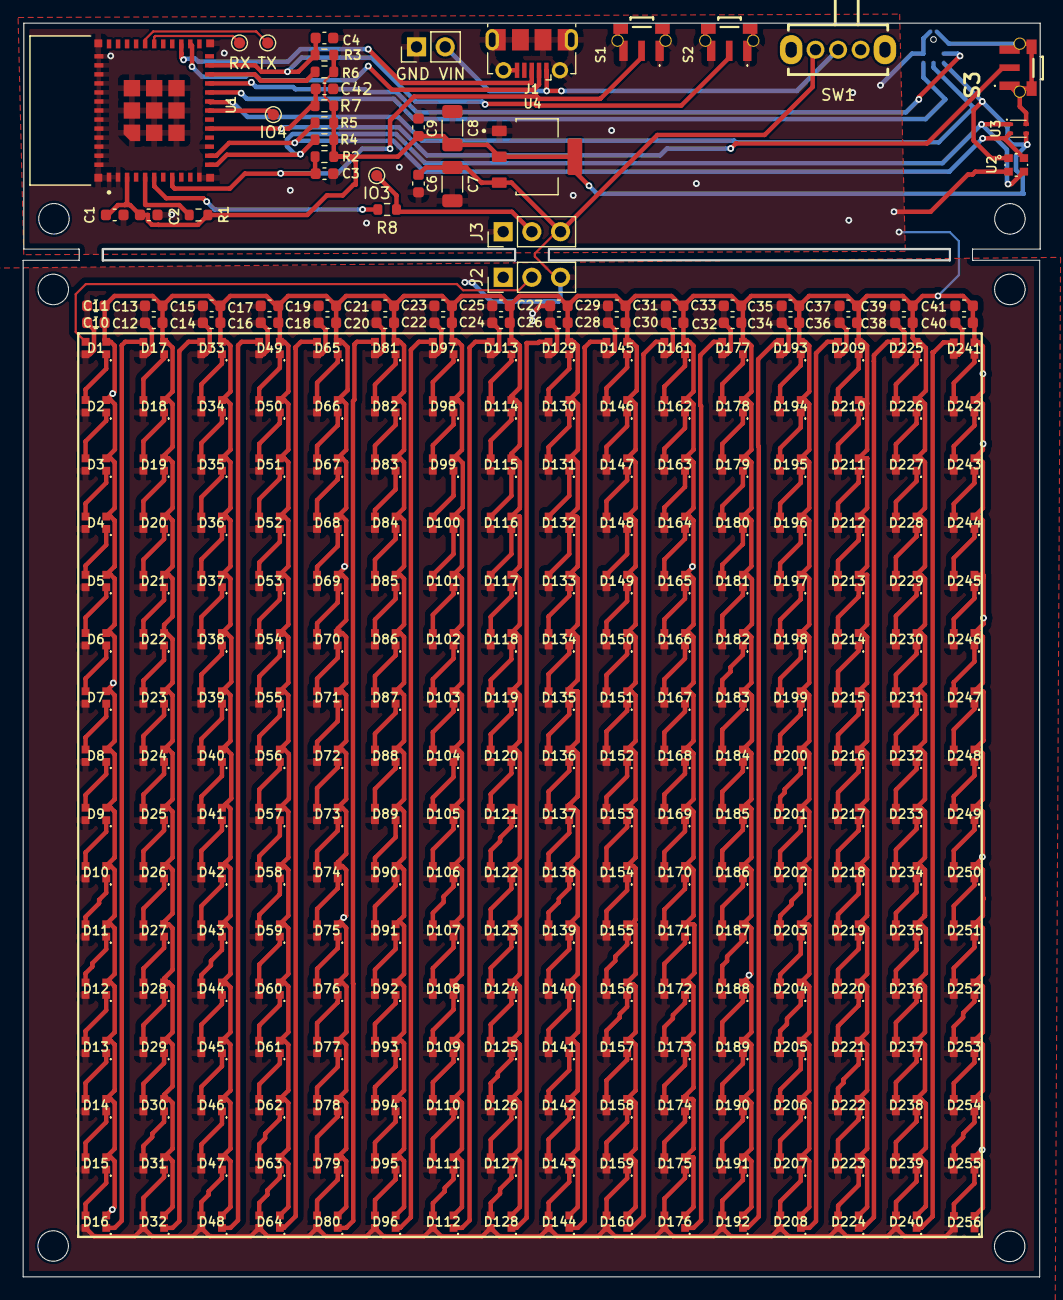
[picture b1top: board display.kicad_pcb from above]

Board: 2 copper layers, 90.1 x 111.0 mm, 328 parts (1 on the bottom side), 277 nets.

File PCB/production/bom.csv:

Designator,Footprint,Quantity,Value,LCSC Part #
C1,0603,1,10uf,CC0603MRX5R6BB106
"C10, C12, C14, C16, C18, C2, C20, C22, C24, C26, C28, C3, C30, C32, C34, C36, C38, C4, C40, C42, C6, C9",0603,22,0.1uf,CC0603KRX7R9BB104
"C11, C13, C15, C17, C19, C21, C23, C25, C27, C29, C31, C33, C35, C37, C39, C41",0603,16,10uf,CC0603KRX7R9BB104
"C7, C8",1206,2,22uf,T55A226M6R3C0500
"D1, D10, D100, D101, D102, D103, D104, D105, D106, D107, D108, D109, D11, D110, D111, D112, D113, D114, D115, D116, D117, D118, D119, D12, D120, D121, D122, D123, D124, D125, D126, D127, D128, D129, D13, D130, D131, D132, D133, D134, D135, D136, D137, D138, D139, D14, D140, D141, D142, D143, D144, D145, D146, D147, D148, D149, D15, D150, D151, D152, D153, D154, D155, D156, D157, D158, D159, D16, D160, D161, D162, D163, D164, D165, D166, D167, D168, D169, D17, D170, D171, D172, D173, D174, D175, D176, D177, D178, D179, D18, D180, D181, D182, D183, D184, D185, D186, D187, D188, D189, D19, D190, D191, D192, D193, D194, D195, D196, D197, D198, D199, D2, D20, D200, D201, D202, D203, D204, D205, D206, D207, D208, D209, D21, D210, D211, D212, D213, D214, D215, D216, D217, D218, D219, D22, D220, D221, D222, D223, D224, D225, D226, D227, D228, D229, D23, D230, D231, D232, D233, D234, D235, D236, D237, D238, D239, D24, D240, D241, D242, D243, D244, D245, D246, D247, D248, D249, D25, D250, D251, D252, D253, D254, D255, D256, D26, D27, D28, D29, D3, D30, D31, D32, D33, D34, D35, D36, D37, D38, D39, D4, D40, D41, D42, D43, D44, D45, D46, D47, D48",WS2812B2020,200,WS2812B-2020,
"D49, D5, D50, D51, D52, D53, D54, D55, D56, D57, D58, D59, D6, D60, D61, D62, D63, D64, D65, D66, D67, D68, D69, D7, D70, D71, D72, D73, D74, D75, D76, D77, D78, D79, D8, D80, D81, D82, D83, D84, D85, D86, D87, D88, D89, D9, D90, D91, D92, D93, D94, D95, D96, D97, D98, D99",WS2812B2020,56,WS2812B-2020,
J1,USB_Micro-B_Molex-105017-0001,1,Micro-USB,105017-0001
"J2, J3",PinHeader_1x03_P2.54mm_Vertical,2,Conn_01x03_Pin,
J4,PinHeader_1x02_P2.54mm_Vertical,1,GND VIN,
MK1,MIC_ICS-43434,1,ICS-43434,ICS-43434
"R1, R2, R3, R6, R7",0603,5,10k,RC0603FR-0710KL
"R4, R5",0603,2,100k,RC0603FR-07100KL
R8,0603,1,0,RC0603FR-0710KL
"S1, S2, S3",SKRTLAE010,3,SKRTLAE010,SKRTLAE010
SW1,SW-TH_SK12D07VG3,1,~,SK12D07VG3
TP1,TestPoint_Pad_D1.0mm,1,IO4,
TP2,TestPoint_Pad_D1.0mm,1,TX,
TP3,TestPoint_Pad_D1.0mm,1,RX,
TP4,TestPoint_Pad_D1.0mm,1,IO3,
U1,XCVR_ESP32-C3-MINI-1-N4,1,ESP32-C3-MINI-1-N4,ESP32-C3-MINI-1-N4
U2,SENSOR_LTR-329ALS-01,1,LTR-329ALS-01,LTR-329ALS-01
U3,SHT4X,1,SHT41-AD1B-R2,SHT41-AD1B-R2
U4,SOT229P700X180-4N,1,AMS1117-3.3,AMS1117-3.3

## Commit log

2025-02-06 Melhorias no case
